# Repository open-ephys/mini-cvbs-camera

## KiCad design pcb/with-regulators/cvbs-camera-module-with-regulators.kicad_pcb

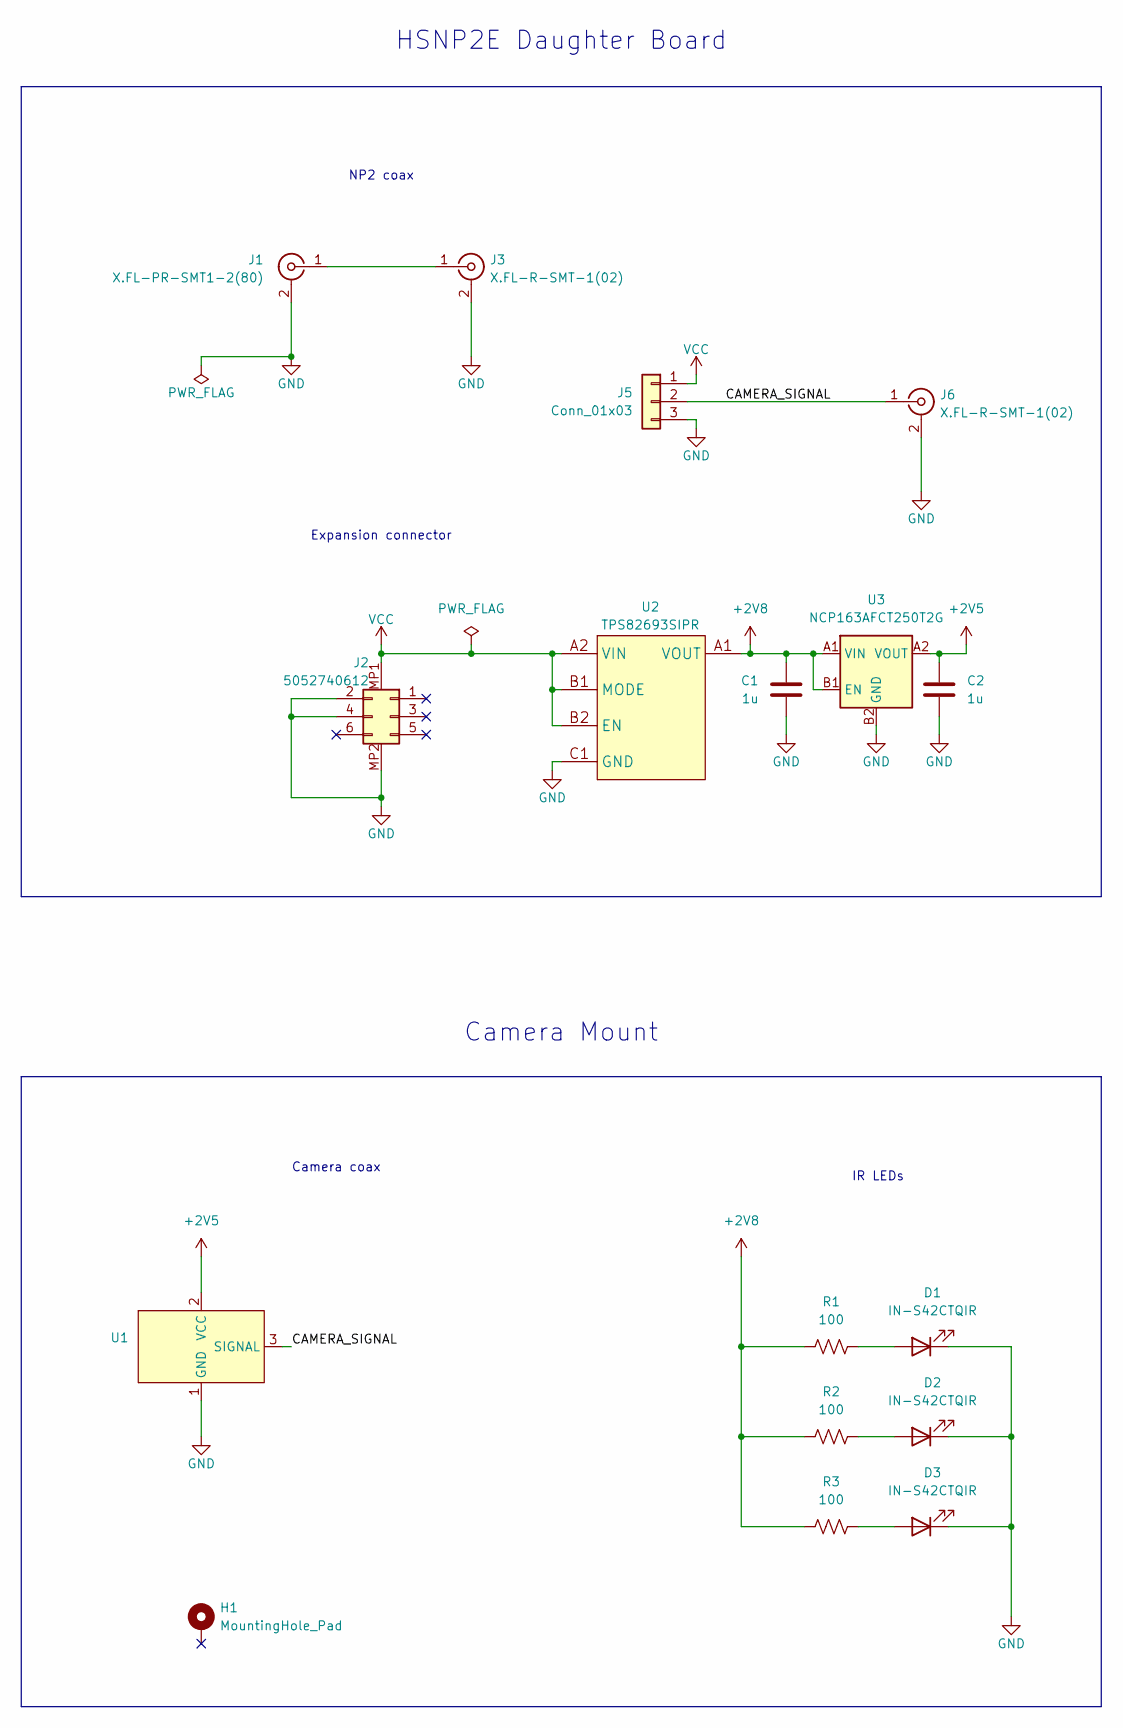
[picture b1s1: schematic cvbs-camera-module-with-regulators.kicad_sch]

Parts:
C1, C2: 1u; C_0201_0603Metric
D1, D2, D3: IN-S42CTQIR; LED_0402_1005Metric
H1: MountingHole_Pad; MountingHole_1.2mm_M1.2_ISO1207_Pad
J1: X.FL-PR-SMT1-2(80); HIROSE_X.FL-PR-SMT1-2
J2: 5052740612; Molex_SlimStack_505413-0610_2x3_P0.35mm_Vertical
J3, J6: X.FL-R-SMT-1(02); HIROSE_X.FL-R-SMT-1
J5: Conn_01x03; camera-solder-points
R1, R2, R3: 100; R_0201_0603Metric
U1: cvbs-camera; 5x5mm_mini-camera
U2: TPS82693SIPR; TI_SIP0008B
U3: NCP163AFCT250T2G; WLCSP-4_0.64x0.64mm_Layout2x2_P0.35mm

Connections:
+2V5: C2.1, U1.2 (VCC), U3.A2 (VOUT)
+2V8: C1.1, R1.1, R2.1, R3.1, U2.A1 (VOUT), U3.A1 (VIN), U3.B1 (EN)
/CAMERA_SIGNAL: J5.2, J6.1 (In), U1.3 (SIGNAL)
GND: C1.2, C2.2, D1.1 (K), D2.1 (K), D3.1 (K), J1.2 (Ext), J2.2, J2.4, J2.MP2, J3.2 (Ext), J5.3, J6.2 (Ext), U1.1 (GND), U2.C1 (GND), U2.C2 (GND), U2.C3 (GND), U3.B2 (GND)
unnamed: D1.2 (A), R1.2
unnamed: D2.2 (A), R2.2
unnamed: D3.2 (A), R3.2
unnamed: J1.1 (In), J3.1 (In)
VCC: J2.MP1, J5.1, U2.A2 (VIN), U2.A3 (VIN), U2.B1 (MODE), U2.B2 (EN)

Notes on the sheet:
Camera Mount
Expansion connector
IR LEDs
HSNP2E Daughter Board
NP2 coax
Camera coax

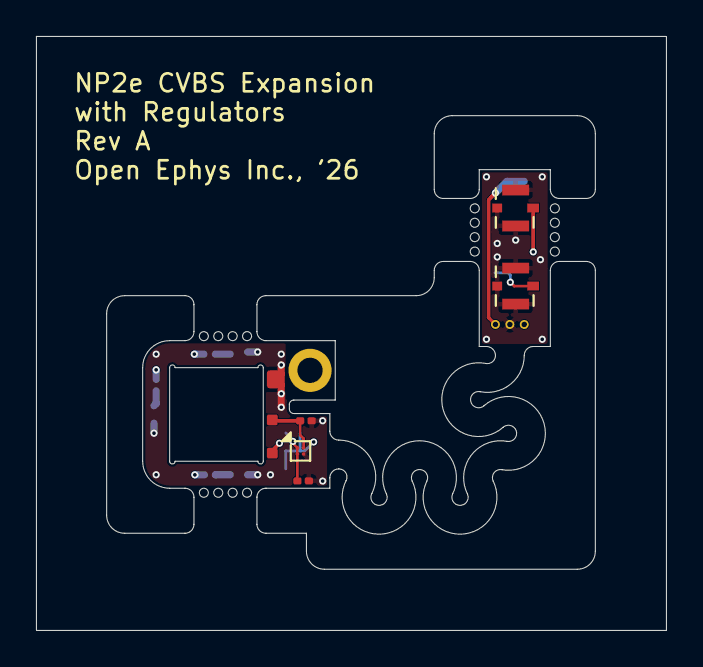
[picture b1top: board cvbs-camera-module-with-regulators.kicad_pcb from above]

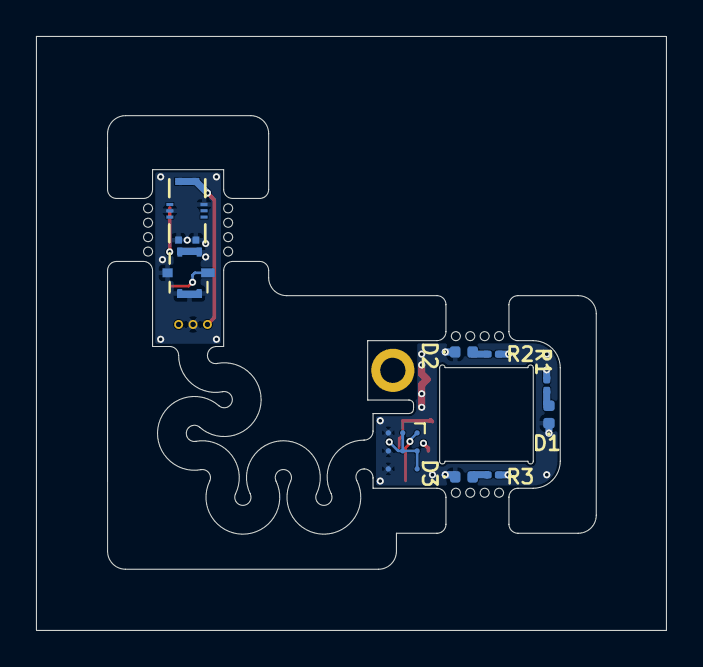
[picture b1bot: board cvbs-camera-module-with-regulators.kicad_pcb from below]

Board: 4 copper layers, 35.0 x 33.0 mm, 17 parts (9 on the bottom side), 9 nets.

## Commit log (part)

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2025-04-30 PCB rev-a initial commit
2025-04-30 Modified Apollo module
    - WIP
    - Snap-fit for np2 hs
    - Cut-out for inductor
    - New camera shoulder + 1DOF arm to be square with PCB parts
    - Arm for minimizing PCB flex
2025-07-11 Design discussed with Aman 2025-07-11
    - 1DoF Camera mount decoupled from Apollo drive
    - Camera & headstage are removed as one unit connected by wire or
    polyamide substrate
2026-05-04 Mechanical and cvbs camera mount pcb for review
    targets 'cvbs' branch of open-ephys-kicad-library
2026-06-10 Address feedback
    - Fill out title blocks
    - LEDs 0201 -> 0402 & assign PN
    - Power LEDs with 2.85V regulator
    - Remove noise on fab layers
    - Thicken flex cable
    - Add .sldprt & .dxf files for flex pattern
